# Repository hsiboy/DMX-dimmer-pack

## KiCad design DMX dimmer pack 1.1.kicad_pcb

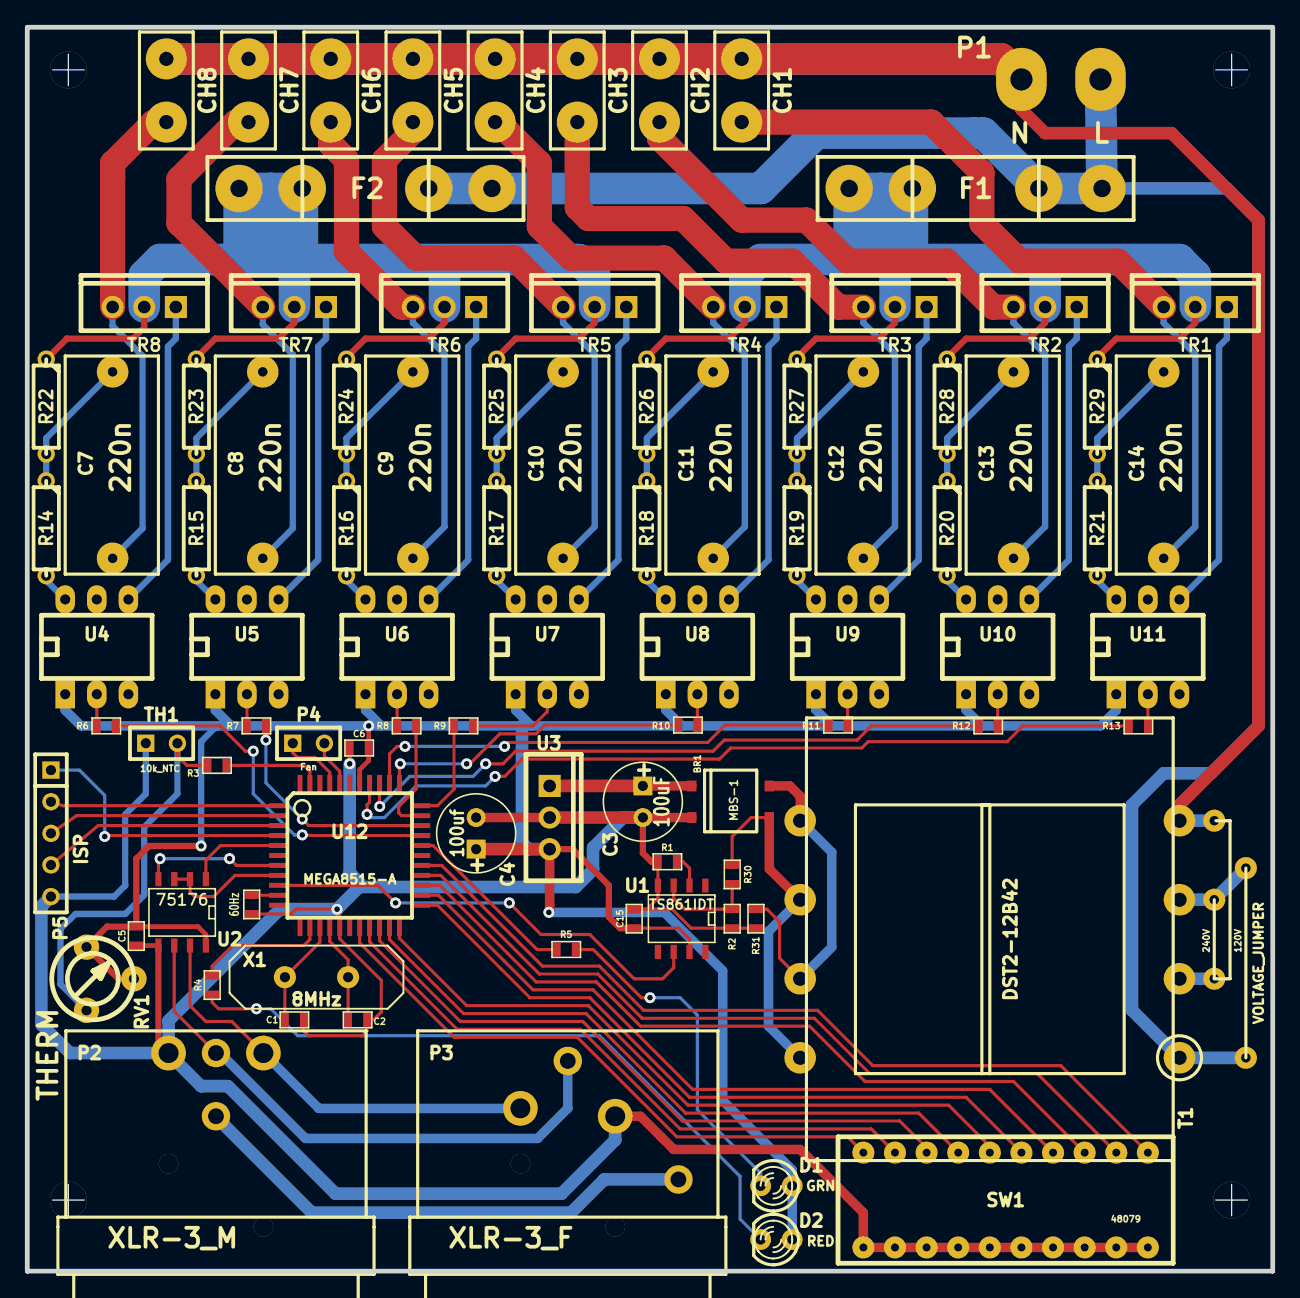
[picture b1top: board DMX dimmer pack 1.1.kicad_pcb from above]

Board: 2 copper layers, 100.1 x 99.9 mm, 95 parts (0 on the bottom side), 93 nets.

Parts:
4/40_screw_hole, 4/40_screw_hole#2, 4/40_screw_hole#3, 4/40_screw_hole#4: VAL**; 4/40_screw_hole
BR1: MBS-1; MBS-1_Rectifier
C1, C2: 27pf; SM0603
C3: 100uF; C1V7
C4: 100uf; C1V7
C5, C6, C15: 1uF; SM0603
C7, C8, C9, C10, C11, C12, C13, C14: 220n; C_ECQ-UAAF224K
CH1, CH2, CH3, CH4, CH5, CH6, CH7, CH8: CONN_2; wire_pair_18AWG_200
D1: GRN; LED-3MM
D2: RED; LED-3MM
F1, F2: 8A; FUSE5-20
J1: VOLTAGE_JUMPER; Voltage_Select_Narrow
JP1: 60Hz; SM0603
P1: MAINS; MATE-N-LOK_250-2
P2: XLR-3_M; XLR3_NC3MAH
P3: XLR-3_F; XLR3_NC3FAH
P4: Fan; SIL-2
P5: ISP; SIL-5
R1, R30: 4.7k; SM0603
R2, R4, R5: 1k; SM0603
R3: 390R; SM0603
R6, R7, R8, R9, R10, R11, R12, R13: 180R; SM0603
R14, R15, R16, R17, R18, R19, R20, R21: 180R; R3
R22, R23, R24, R25, R26, R27, R28, R29: 1.2k; R3
R31: 10k; SM0603
RV1: 10k; POT20x15V
SW1: DIPS_10; DIPS-DS10
T1: DST2-12B42
TH1: 10k_NTC; SIL-2
TR1, TR2, TR3, TR4, TR5, TR6, TR7, TR8: BTA08; TO220_VERT
U1: TS861IDT; SO8E
U2: 75176; SO8E
U3: 7805; LM78xx_TO220_VERT
U4, U5, U6, U7, U8, U9, U10, U11: MOC3021; DIP-6__300_ELL
U12: MEGA8515-A; TQFP44
X1: 8MHz; HC-18UV

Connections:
+5V: C4.1, C5.1, C6.1, C15.1, D1.1, D2.1, RV1.1, RV1.2, U1.7, U2.8, U3.VO, U4.1, U5.1, U6.1, U7.1, U8.1, U9.1, U10.1, U11.1, U12.38
GND: BR1.-, C1.2, C2.2, C3.2, C4.2, C5.2, C6.2, C15.2, JP1.2, P2.1, P3.1, P5.5, R1.1, R2.1, R31.1, SW1.1, SW1.2, SW1.3, SW1.4, SW1.5, SW1.6, SW1.7, SW1.8, SW1.9, SW1.10, TH1.1, U1.4, U2.5, U3.Gnd, U12.16
L: F1.2, F2.2, J1.1, P1.1, T1.1
N: CH1.2, CH2.2, CH3.2, CH4.2, CH5.2, CH6.2, CH7.2, CH8.2, J1.2, P1.2, T1.4
unnamed: P5.3, U12.2
unnamed: P5.1, U12.4
unnamed: U2.1, U12.5
unnamed: R7.2, U12.31
unnamed: P4.1, U12.41
unnamed: P2.2, P3.2, U2.7
unnamed: P2.4, P3.4
unnamed: C11.1, R18.1, R26.2
unnamed: C11.2, CH4.1, TR4.1
unnamed: TR4.3, U8.4
unnamed: R18.2, U8.6
unnamed: R20.2, U10.6
unnamed: C13.2, CH2.1, TR2.1
unnamed: R12.2, U12.36
unnamed: R9.2, U12.33
unnamed: R11.2, U12.35
unnamed: R3.2, U12.43
unnamed: R13.2, U12.37
unnamed: R1.2, U1.2
unnamed: U1.6, U12.9
unnamed: J1.4, T1.3
unnamed: JP1.1, U12.10
unnamed: P5.2, U12.1
unnamed: R2.2, R30.2, U1.3
unnamed: F1.1, R26.1, R27.1, R28.1, R29.1, TR1.2, TR2.2, TR3.2, TR4.2
unnamed: P4.2, U12.40
unnamed: SW1.20, U12.18
unnamed: SW1.11, U12.27
unnamed: SW1.13, U12.25
unnamed: SW1.14, U12.24
unnamed: SW1.15, U12.23
unnamed: SW1.16, U12.22
unnamed: SW1.17, U12.21
unnamed: SW1.18, U12.20
unnamed: SW1.19, U12.19
unnamed: R12.1, U10.2
unnamed: R5.1, U12.29
unnamed: C1.1, U12.14, X1.2
unnamed: D1.2, R5.2
unnamed: D2.2, R4.1
unnamed: R4.2, U12.13
unnamed: C2.1, U12.15, X1.1
unnamed: R10.1, U8.2
unnamed: R6.1, U4.2
unnamed: TR8.3, U4.4
unnamed: R14.2, U4.6
unnamed: C14.2, CH1.1, TR1.1
unnamed: R13.1, U11.2
unnamed: TR1.3, U11.4
unnamed: R21.2, U11.6
unnamed: R9.1, U7.2
unnamed: R17.2, U7.6
unnamed: C10.2, CH5.1, TR5.1
unnamed: TR2.3, U10.4
unnamed: C13.1, R20.1, R28.2
unnamed: C12.2, CH3.1, TR3.1
unnamed: TR5.3, U7.4
unnamed: R11.1, U9.2
unnamed: TR3.3, U9.4
unnamed: R19.2, U9.6
unnamed: F2.1, R22.1, R23.1, R24.1, R25.1, TR5.2, TR6.2, TR7.2, TR8.2
unnamed: R8.1, U6.2
unnamed: TR6.3, U6.4
unnamed: R16.2, U6.6
unnamed: U2.2, U2.3, U12.8
unnamed: U2.4, U12.7
unnamed: P2.3, P3.3, U2.6
unnamed: C10.1, R17.1, R25.2
unnamed: R7.1, U5.2
unnamed: R15.2, U5.6
unnamed: C8.2, CH7.1, TR7.1
unnamed: TR7.3, U5.4
unnamed: C8.1, R15.1, R23.2
unnamed: C7.2, CH8.1, TR8.1
unnamed: C9.2, CH6.1, TR6.1
unnamed: C12.1, R19.1, R27.2
unnamed: R10.2, U12.34
unnamed: R8.2, U12.32
unnamed: R6.2, U12.30
unnamed: C7.1, R14.1, R22.2
unnamed: C9.1, R16.1, R24.2
unnamed: C14.1, R21.1, R29.2
unnamed: BR1.AC2, R30.1, T1.5, T1.7
unnamed: P5.4, U12.3
unnamed: R3.1, RV1.3, TH1.2
unnamed: BR1.AC1, R31.2, T1.6, T1.8
unnamed: J1.3, T1.2
unnamed: BR1.+, C3.1, U3.VI
unnamed: SW1.12, U12.26

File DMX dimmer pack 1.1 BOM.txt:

#Cmp ( order = Reference )
| BR1        MBS-1       	             
| C1         27pf     	0603  	             
| C2         27pf      	0603  	             
| C3         100uF                    
| C4         100uf                    
| C5         1uF       	0603  	              
| C6         1uF       	0603  	  
| C15        1uF       	0603  	               
| C7         220n   	ECQ-UAAF224K               
| C8         220n   	ECQ-UAAF224K             
| C9         220n       ECQ-UAAF224K             
| C10        220n       ECQ-UAAF224K             
| C11        220n       ECQ-UAAF224K             
| C12        220n       ECQ-UAAF224K             
| C13        220n       ECQ-UAAF224K             
| C14        220n       ECQ-UAAF224K             
| D1         GRN        3mm LED             
| D2         RED        3mm LED             
| F1         8A         5x20mm fuse             
| F2         8A         5x20mm fuse             
             
| JP1        60Hz       0603 0-Ohm                          
| P2         XLR-3_M    Neutrik NC3MAH             
| P3         XLR-3_F    Neutrik NC3FAH             
             
            
| R1         4.7k       0603            
| R2         1k         0603           
| R3         390R       0603            
| R4         1k         0603             
| R5         1k         0603             
| R6         180R       0603             
| R7         180R       0603            
| R8         180R       0603             
| R9         180R       0603            
| R10        180R       0603           
| R11        180R       0603             
| R12        180R       0603             
| R13        180R       0603              
| R14        180R       0.25W            
| R15        180R       0.25W             
| R16        180R       0.25W             
| R17        180R       0.25W            
| R18        180R       0.25W            
| R19        180R       0.25W            
| R20        180R       0.25W             
| R21        180R       0.25W            
| R22        1.2k       0.25W             
| R23        1.2k       0.25W             
| R24        1.2k       0.25W            
| R25        1.2k       0.25W             
| R26        1.2k       0.25W             
| R27        1.2k       0.25W             
| R28        1.2k       0.25W             
| R29        1.2k       0.25W             
| R30        4.7k       0603             
| R31        10k        0603            
| RV1        10k                     
| SW1        DIPS_10                  
| T1         DST2-12B42               
| TH1        10k NTC                  
| TR1        BTA08      TO220 Triac (Isolated tab)           
| TR2        BTA08      TO220 Triac (Isolated tab)
| TR3        BTA08      TO220 Triac (Isolated tab)         
| TR4        BTA08      TO220 Triac (Isolated tab)             
| TR5        BTA08      TO220 Triac (Isolated tab)            
| TR6        BTA08      TO220 Triac (Isolated tab)           
| TR7        BTA08      TO220 Triac (Isolated tab)          
| TR8        BTA08      TO220 Triac (Isolated tab)
| U1         TS861IDT   SO-8           
| U2         75176      SO-8         
| U3         7805       TO-220           
| U4         MOC3021    DIP-6 Random-phase triac opto coupler           
| U5         MOC3021    DIP-6 Random-phase triac opto coupler           
| U6         MOC3021    DIP-6 Random-phase triac opto coupler             
| U7         MOC3021    DIP-6 Random-phase triac opto coupler           
| U8         MOC3021    DIP-6 Random-phase triac opto coupler          
| U9         MOC3021    DIP-6 Random-phase triac opto coupler             
| U10        MOC3021    DIP-6 Random-phase triac opto coupler            
| U11        MOC3021    DIP-6 Random-phase triac opto coupler            
| U12        MEGA8515-A TQFP44
| X1         8MHz       Crystal

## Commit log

2015-01-14 initial checkin
2015-01-14 unpacked src, cleaned up repo

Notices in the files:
DMX dimmer pack 1.1.kicad_pcb:
V1.0 © 2015 Stuart Taylor @hsiboy
